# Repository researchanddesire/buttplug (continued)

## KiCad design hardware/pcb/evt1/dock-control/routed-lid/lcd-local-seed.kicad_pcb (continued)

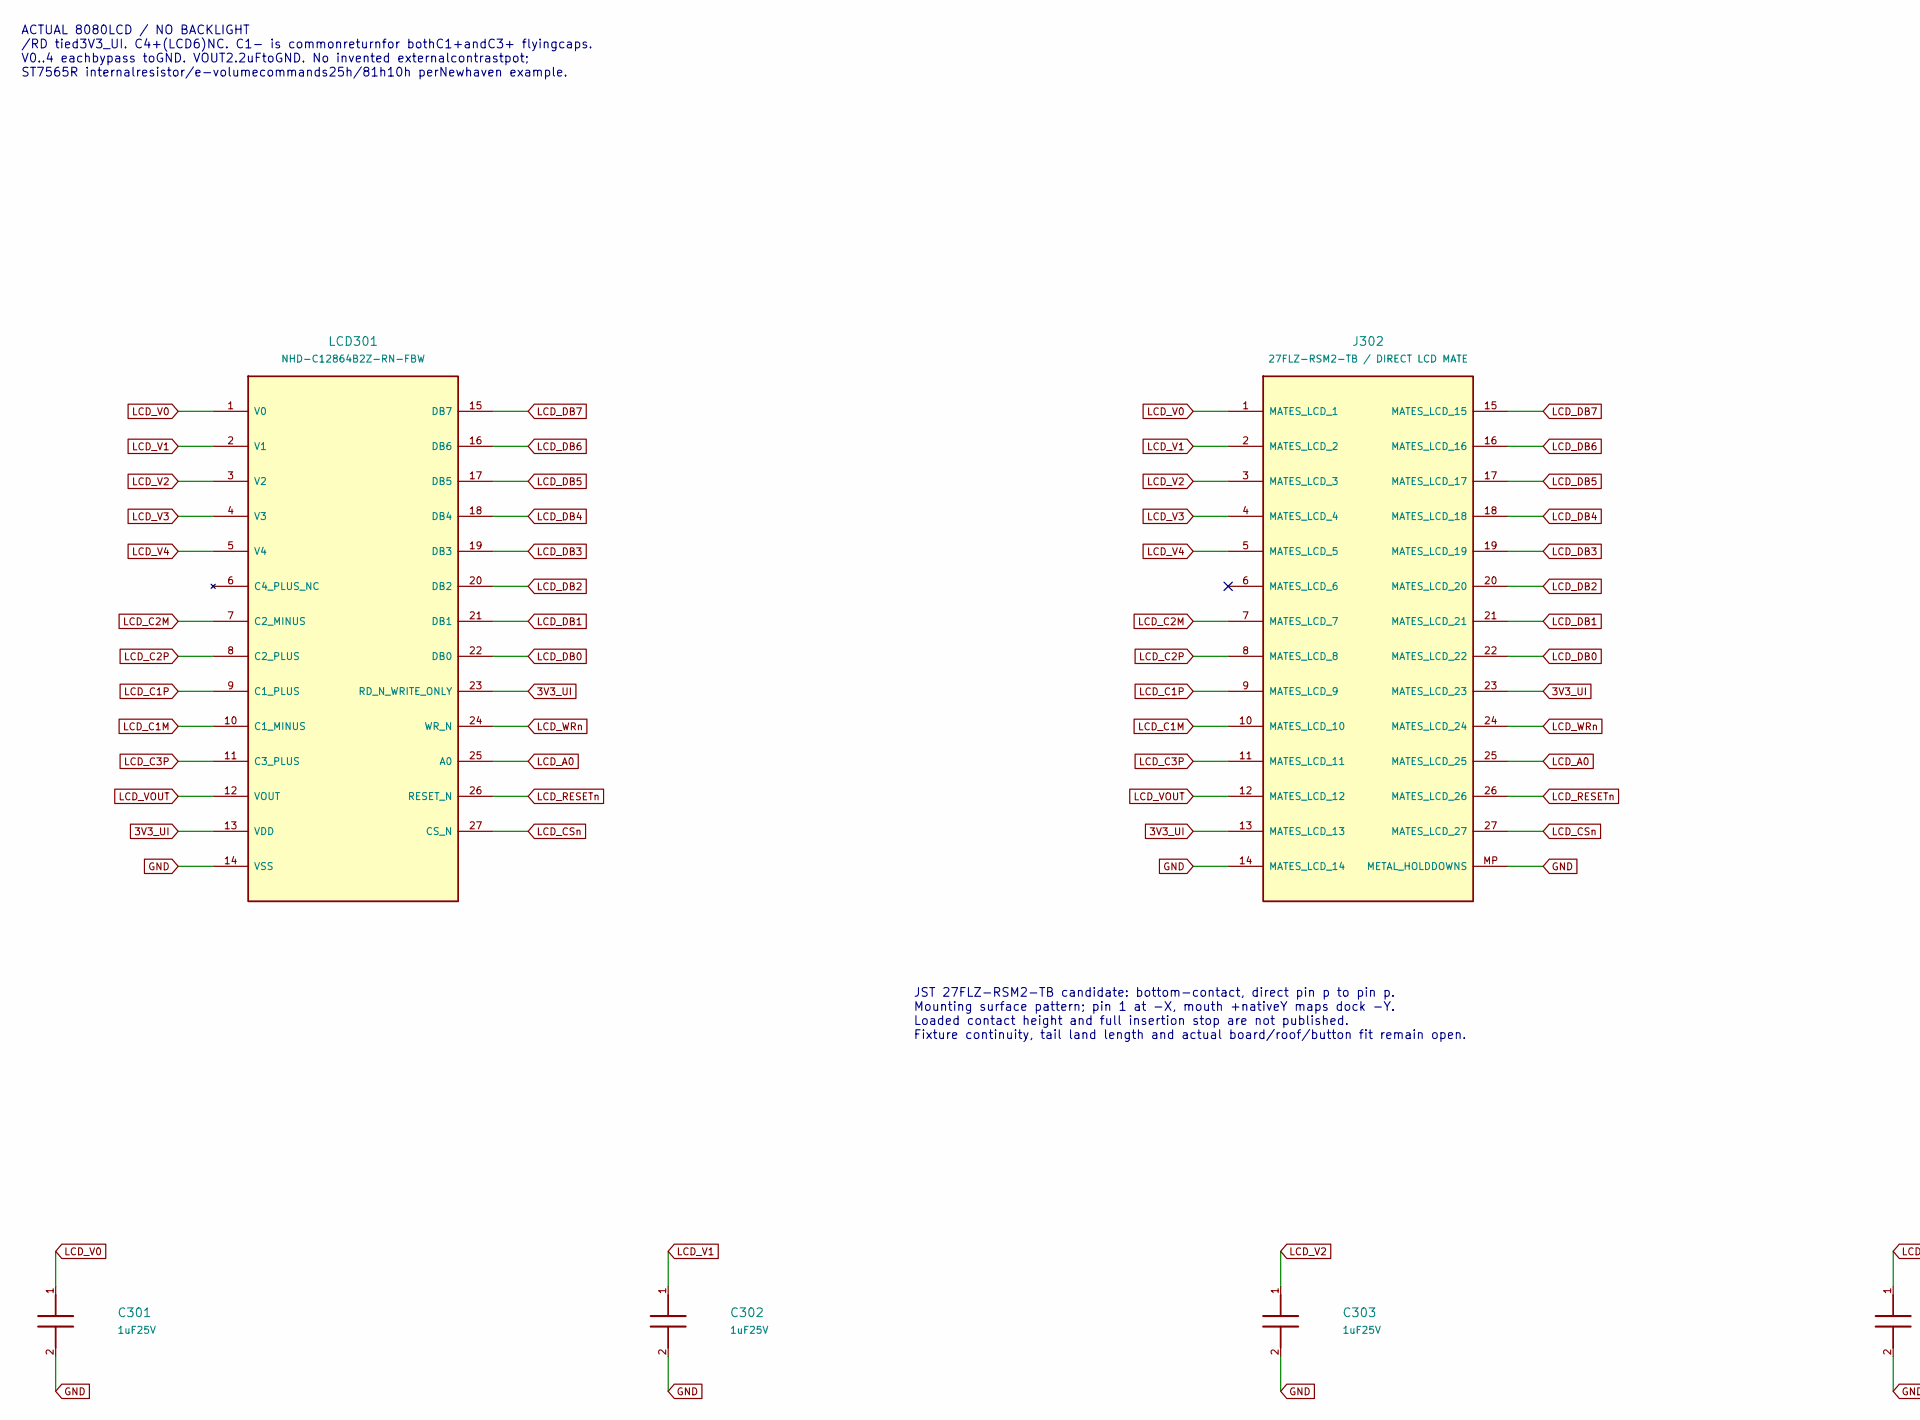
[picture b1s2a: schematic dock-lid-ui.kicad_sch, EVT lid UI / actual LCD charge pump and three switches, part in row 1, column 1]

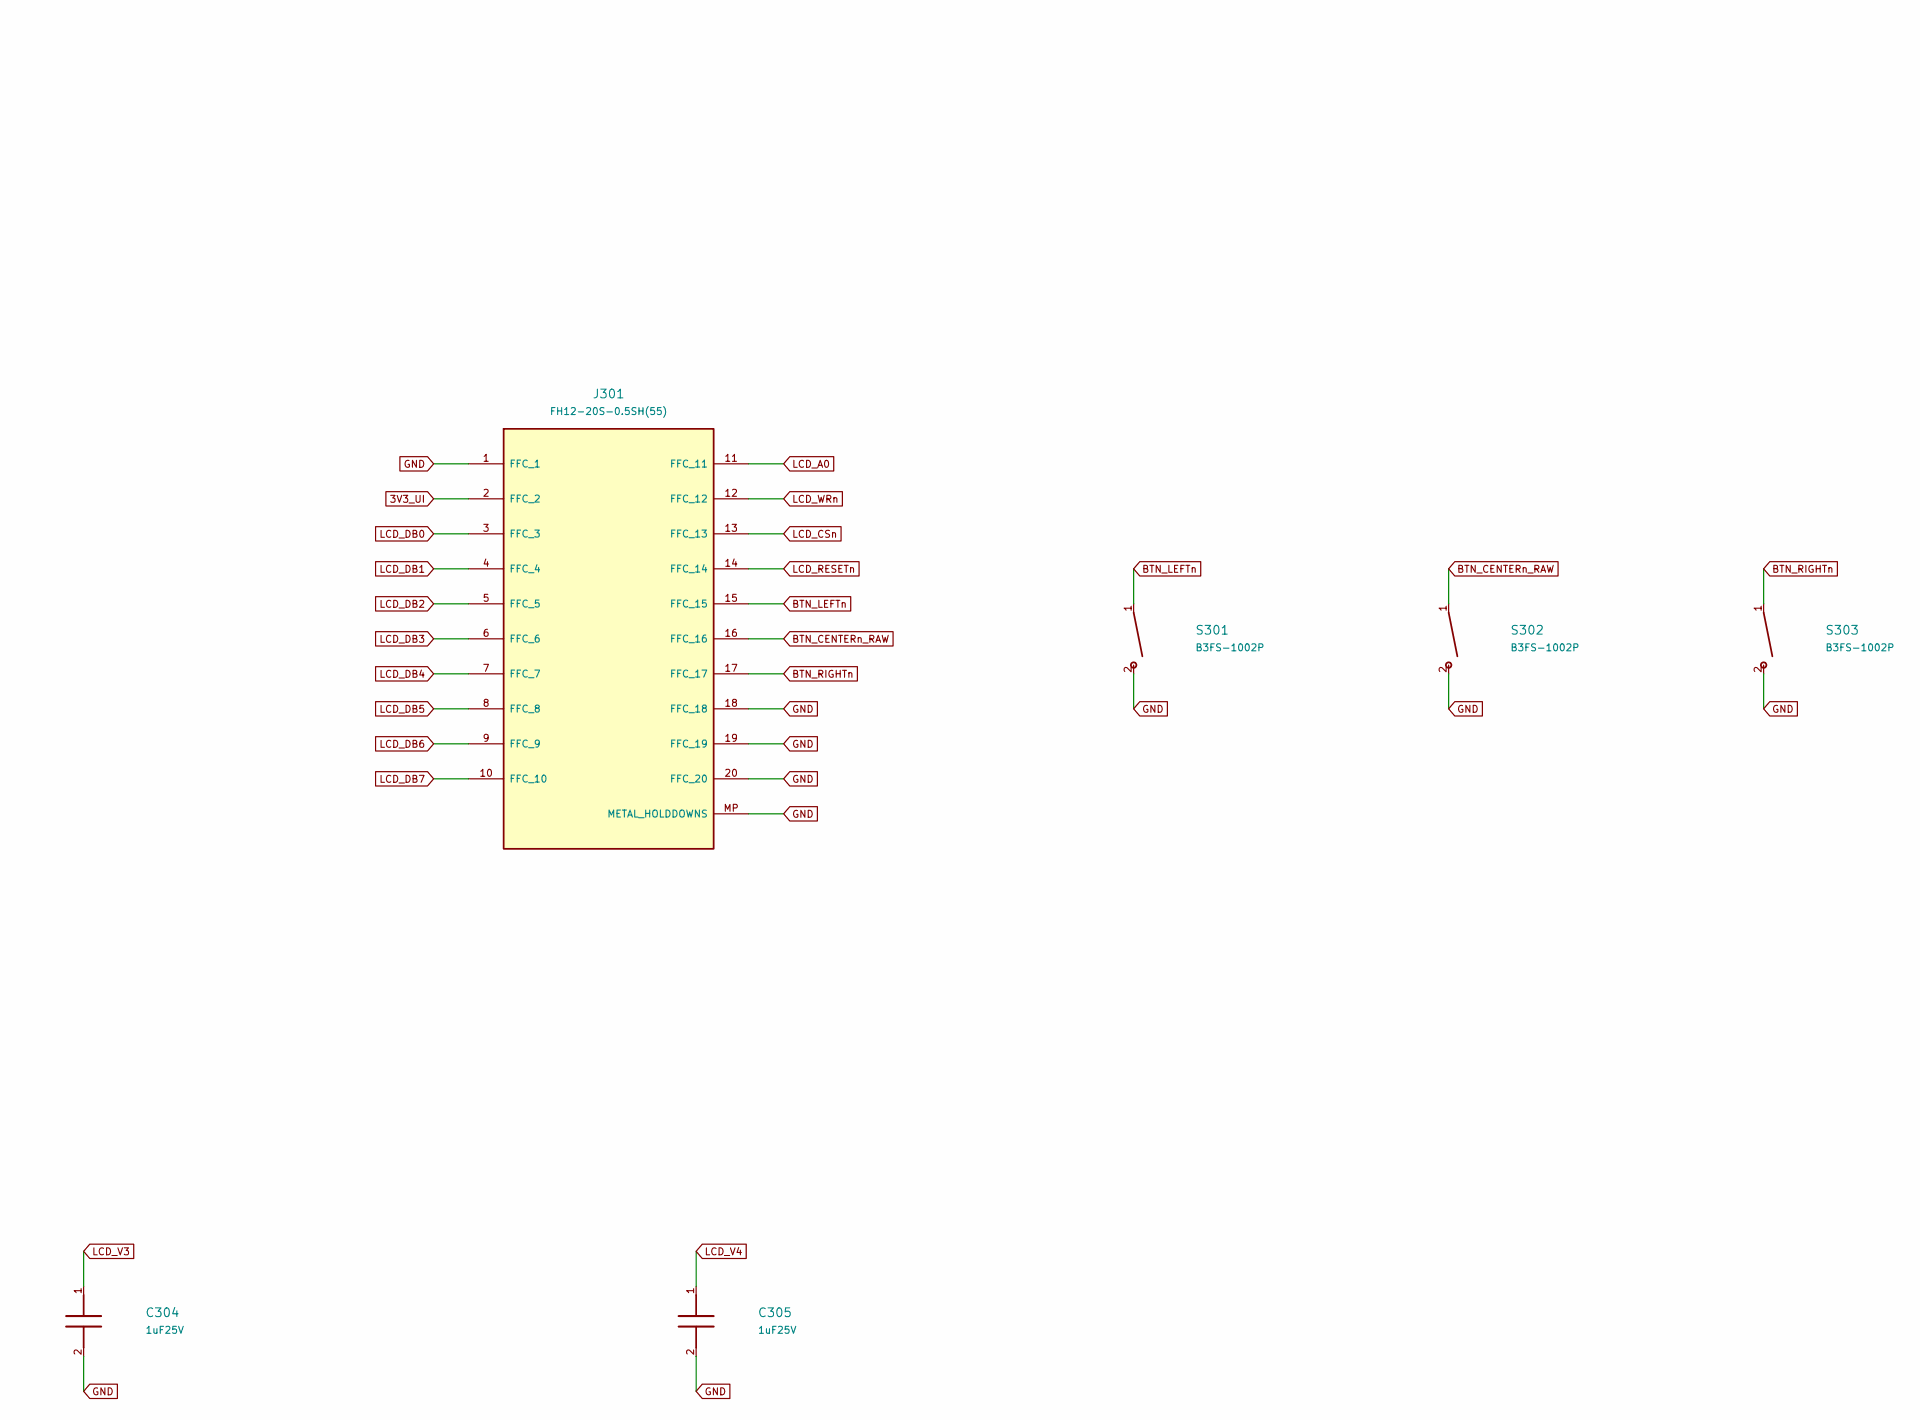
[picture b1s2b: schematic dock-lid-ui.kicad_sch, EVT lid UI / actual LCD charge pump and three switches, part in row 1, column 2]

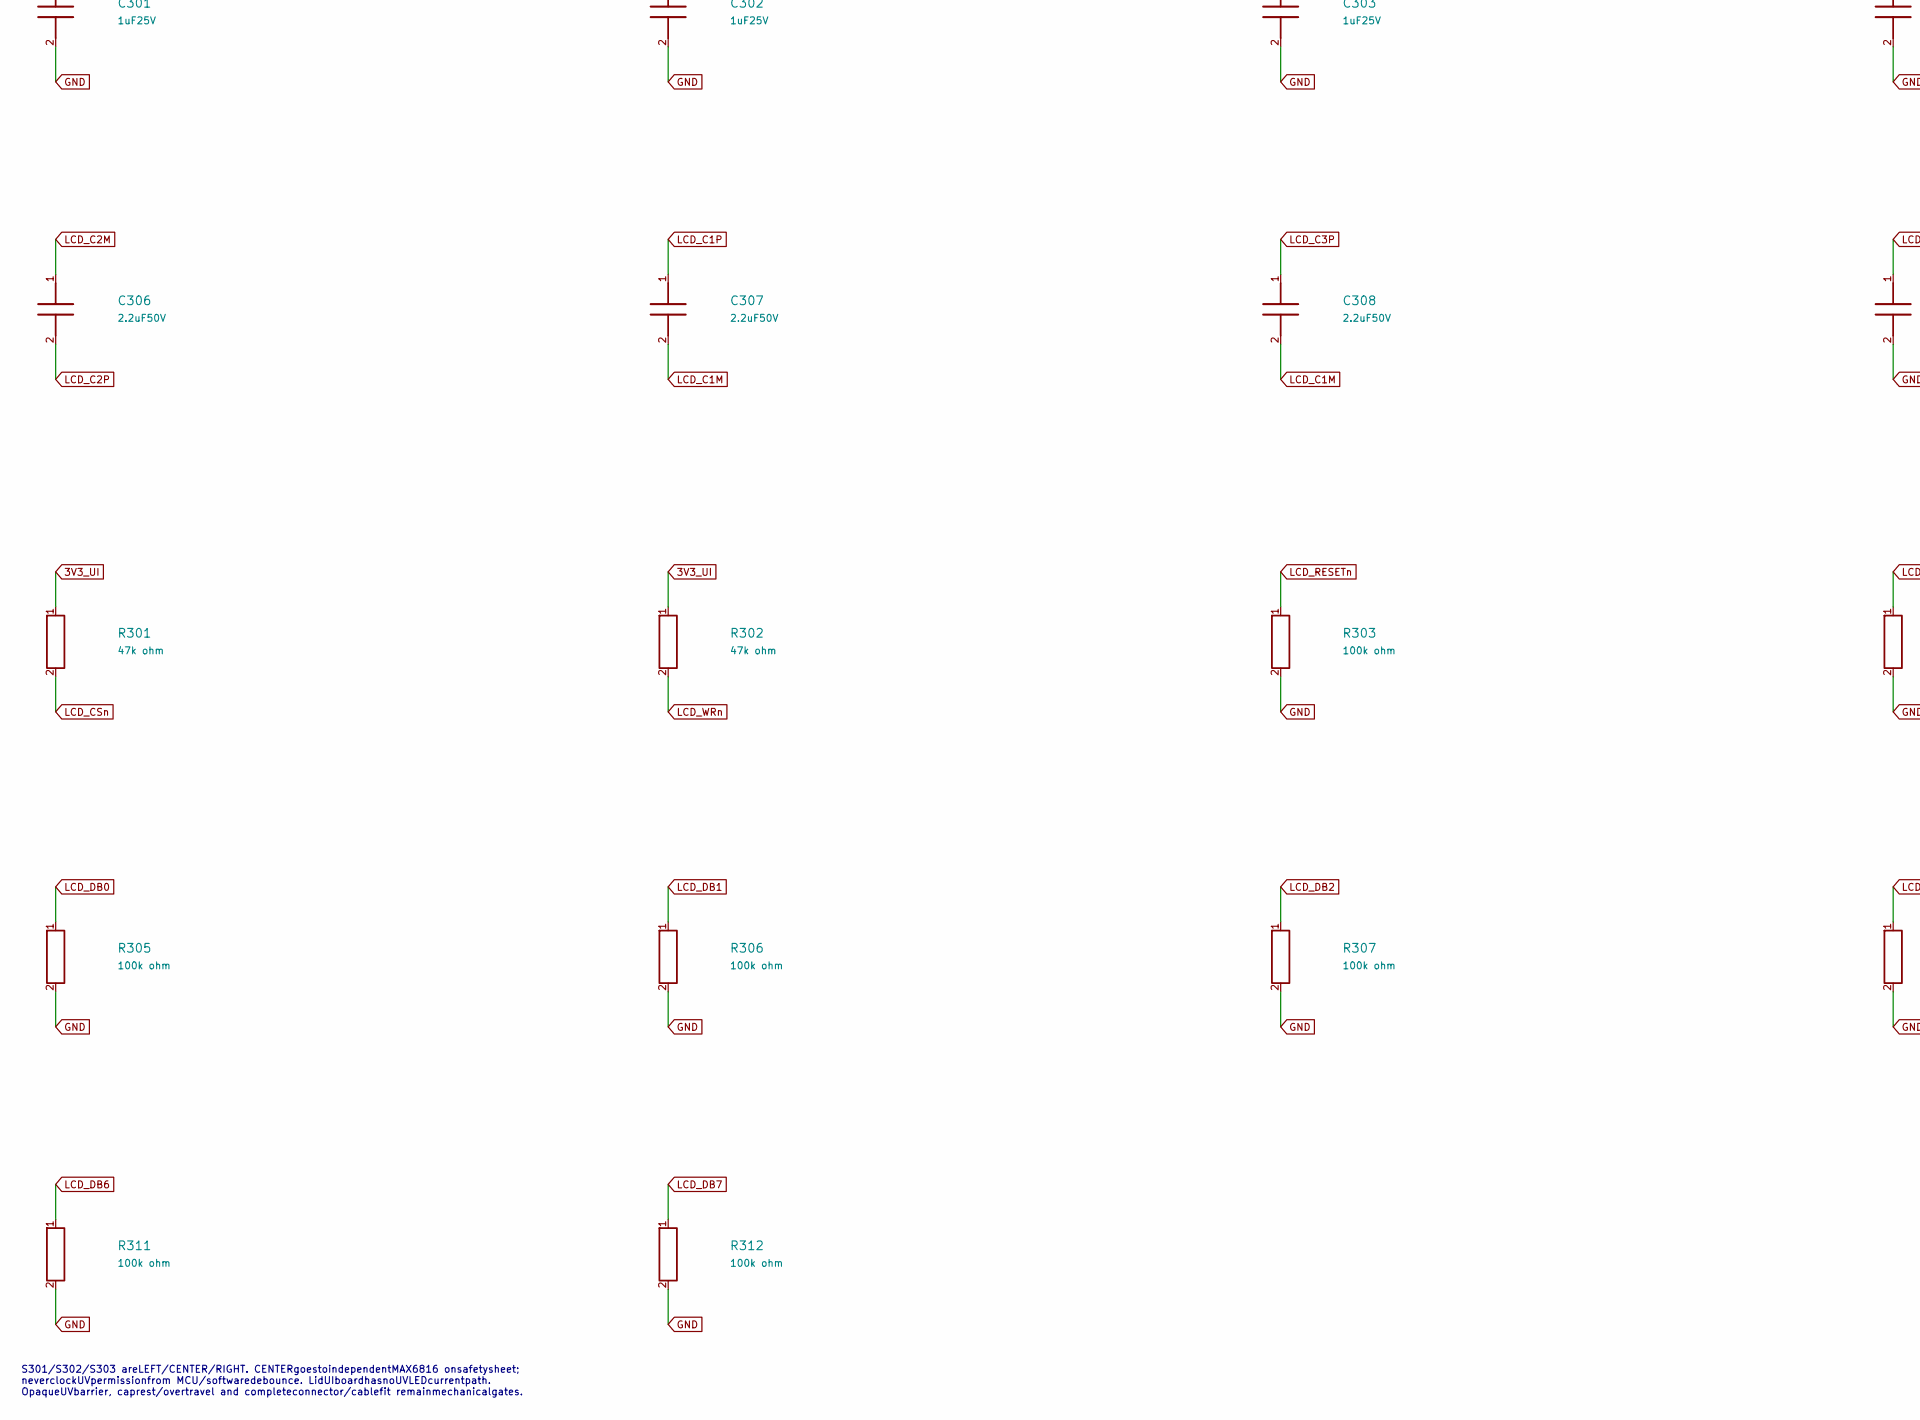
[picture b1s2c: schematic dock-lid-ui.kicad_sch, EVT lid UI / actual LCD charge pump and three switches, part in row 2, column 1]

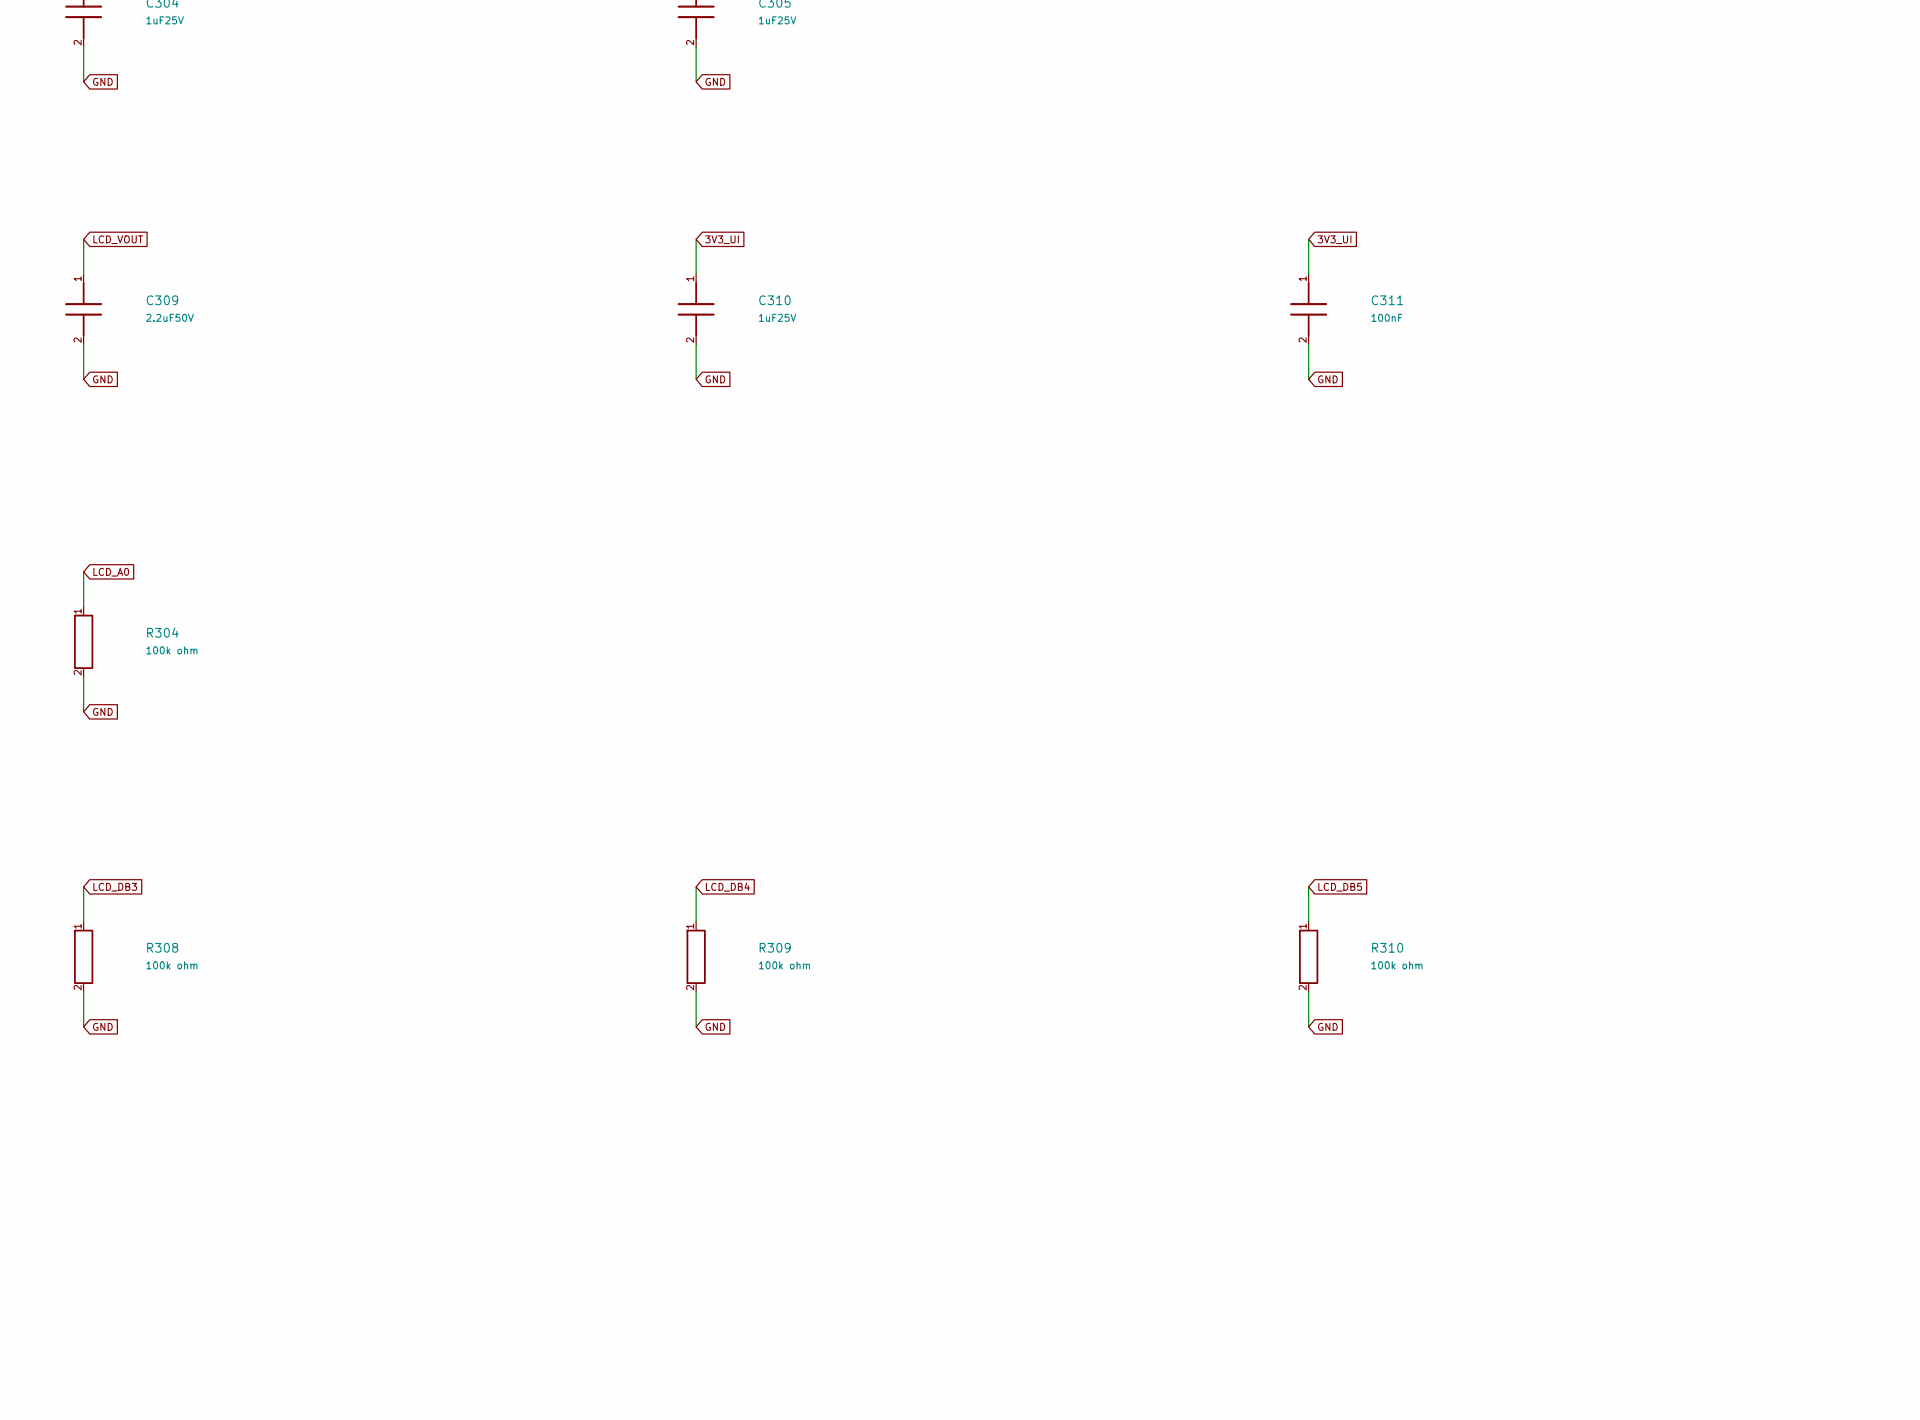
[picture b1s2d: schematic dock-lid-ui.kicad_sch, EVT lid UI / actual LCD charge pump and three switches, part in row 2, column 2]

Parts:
C301, C302, C303, C304, C305, C310: 1uF25V; C_0603_1608Metric; MPN C1608X7R1E105K080AB
C306, C307, C308, C309: 2.2uF50V; C_1206_3216Metric; MPN C3216X7R1H225K160AB
C311: 100nF; C_0402_1005Metric; MPN GRM155R71C104KA88D
J301: FH12-20S-0.5SH(55); Hirose_FH12-20S-0.5SH_1x20-1MP_P0.50mm_Horizontal; MPN FH12-20S-0.5SH(55)
J302: 27FLZ-RSM2-TB / DIRECT LCD MATE; JST_27FLZ-RSM2-TB_1x27_P0.50mm_BottomContact; MPN 27FLZ-RSM2-TB
LCD301: NHD-C12864B2Z-RN-FBW; MPN NHD-C12864B2Z-RN-FBW
R301, R302: 47k ohm; R_0603_1608Metric; MPN RC0603FR-0747KL
R303, R304, R305, R306, R307, R308, R309, R310, R311, R312: 100k ohm; R_0603_1608Metric; MPN RC0603FR-07100KL
S301, S302, S303: B3FS-1002P; SW_SPST_Omron_B3FS-100xP; MPN B3FS-1002P

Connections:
3V3_UI: C310.1, C311.1, J301.2 (FFC_2), J302.13 (MATES_LCD_13), J302.23 (MATES_LCD_23), LCD301.13 (VDD), LCD301.23 (RD_N_WRITE_ONLY), R301.1, R302.1
BTN_CENTERn_RAW: J301.16 (FFC_16), S302.1
BTN_LEFTn: J301.15 (FFC_15), S301.1
BTN_RIGHTn: J301.17 (FFC_17), S303.1
GND: C301.2, C302.2, C303.2, C304.2, C305.2, C309.2, C310.2, C311.2, J301.1 (FFC_1), J301.18 (FFC_18), J301.19 (FFC_19), J301.20 (FFC_20), J301.MP (METAL_HOLDDOWNS), J302.14 (MATES_LCD_14), J302.MP (METAL_HOLDDOWNS), LCD301.14 (VSS), R303.2, R304.2, R305.2, R306.2, R307.2, R308.2, R309.2, R310.2, R311.2, R312.2, S301.2, S302.2, S303.2
LCD_A0: J301.11 (FFC_11), J302.25 (MATES_LCD_25), LCD301.25 (A0), R304.1
LCD_C1M: C307.2, C308.2, J302.10 (MATES_LCD_10), LCD301.10 (C1_MINUS)
LCD_C1P: C307.1, J302.9 (MATES_LCD_9), LCD301.9 (C1_PLUS)
LCD_C2M: C306.1, J302.7 (MATES_LCD_7), LCD301.7 (C2_MINUS)
LCD_C2P: C306.2, J302.8 (MATES_LCD_8), LCD301.8 (C2_PLUS)
LCD_C3P: C308.1, J302.11 (MATES_LCD_11), LCD301.11 (C3_PLUS)
LCD_CSn: J301.13 (FFC_13), J302.27 (MATES_LCD_27), LCD301.27 (CS_N), R301.2
LCD_DB0: J301.3 (FFC_3), J302.22 (MATES_LCD_22), LCD301.22 (DB0), R305.1
LCD_DB1: J301.4 (FFC_4), J302.21 (MATES_LCD_21), LCD301.21 (DB1), R306.1
LCD_DB2: J301.5 (FFC_5), J302.20 (MATES_LCD_20), LCD301.20 (DB2), R307.1
LCD_DB3: J301.6 (FFC_6), J302.19 (MATES_LCD_19), LCD301.19 (DB3), R308.1
LCD_DB4: J301.7 (FFC_7), J302.18 (MATES_LCD_18), LCD301.18 (DB4), R309.1
LCD_DB5: J301.8 (FFC_8), J302.17 (MATES_LCD_17), LCD301.17 (DB5), R310.1
LCD_DB6: J301.9 (FFC_9), J302.16 (MATES_LCD_16), LCD301.16 (DB6), R311.1
LCD_DB7: J301.10 (FFC_10), J302.15 (MATES_LCD_15), LCD301.15 (DB7), R312.1
LCD_RESETn: J301.14 (FFC_14), J302.26 (MATES_LCD_26), LCD301.26 (RESET_N), R303.1
LCD_V0: C301.1, J302.1 (MATES_LCD_1), LCD301.1 (V0)
LCD_V1: C302.1, J302.2 (MATES_LCD_2), LCD301.2 (V1)
LCD_V2: C303.1, J302.3 (MATES_LCD_3), LCD301.3 (V2)
LCD_V3: C304.1, J302.4 (MATES_LCD_4), LCD301.4 (V3)
LCD_V4: C305.1, J302.5 (MATES_LCD_5), LCD301.5 (V4)
LCD_VOUT: C309.1, J302.12 (MATES_LCD_12), LCD301.12 (VOUT)
LCD_WRn: J301.12 (FFC_12), J302.24 (MATES_LCD_24), LCD301.24 (WR_N), R302.2

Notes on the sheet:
ACTUAL 8080LCD / NO BACKLIGHT /RD tied3V3_UI. C4+(LCD6)NC. C1- is commonreturnfor bothC1+andC3+ flyingcaps. V0..4 eachbypass toGND. VOUT2.2uFtoGND. No invented externalcontrastpot; ST7565R internalresistor/e-volumecommands25h/81h10h perNewhaven example.
JST 27FLZ-RSM2-TB candidate: bottom-contact, direct pin p to pin p. Mounting surface pattern; pin 1 at -X, mouth +nativeY maps dock -Y. Loaded contact height and full insertion stop are not published. Fixture continuity, tail land length and actual board/roof/button fit remain open.
S301/S302/S303 areLEFT/CENTER/RIGHT. CENTERgoestoindependentMAX6816 onsafetysheet; neverclockUVpermissionfrom MCU/softwaredebounce. LidUIboardhasnoUVLEDcurrentpath. OpaqueUVbarrier, caprest/overtravel and completeconnector/cablefit remainmechanicalgates.

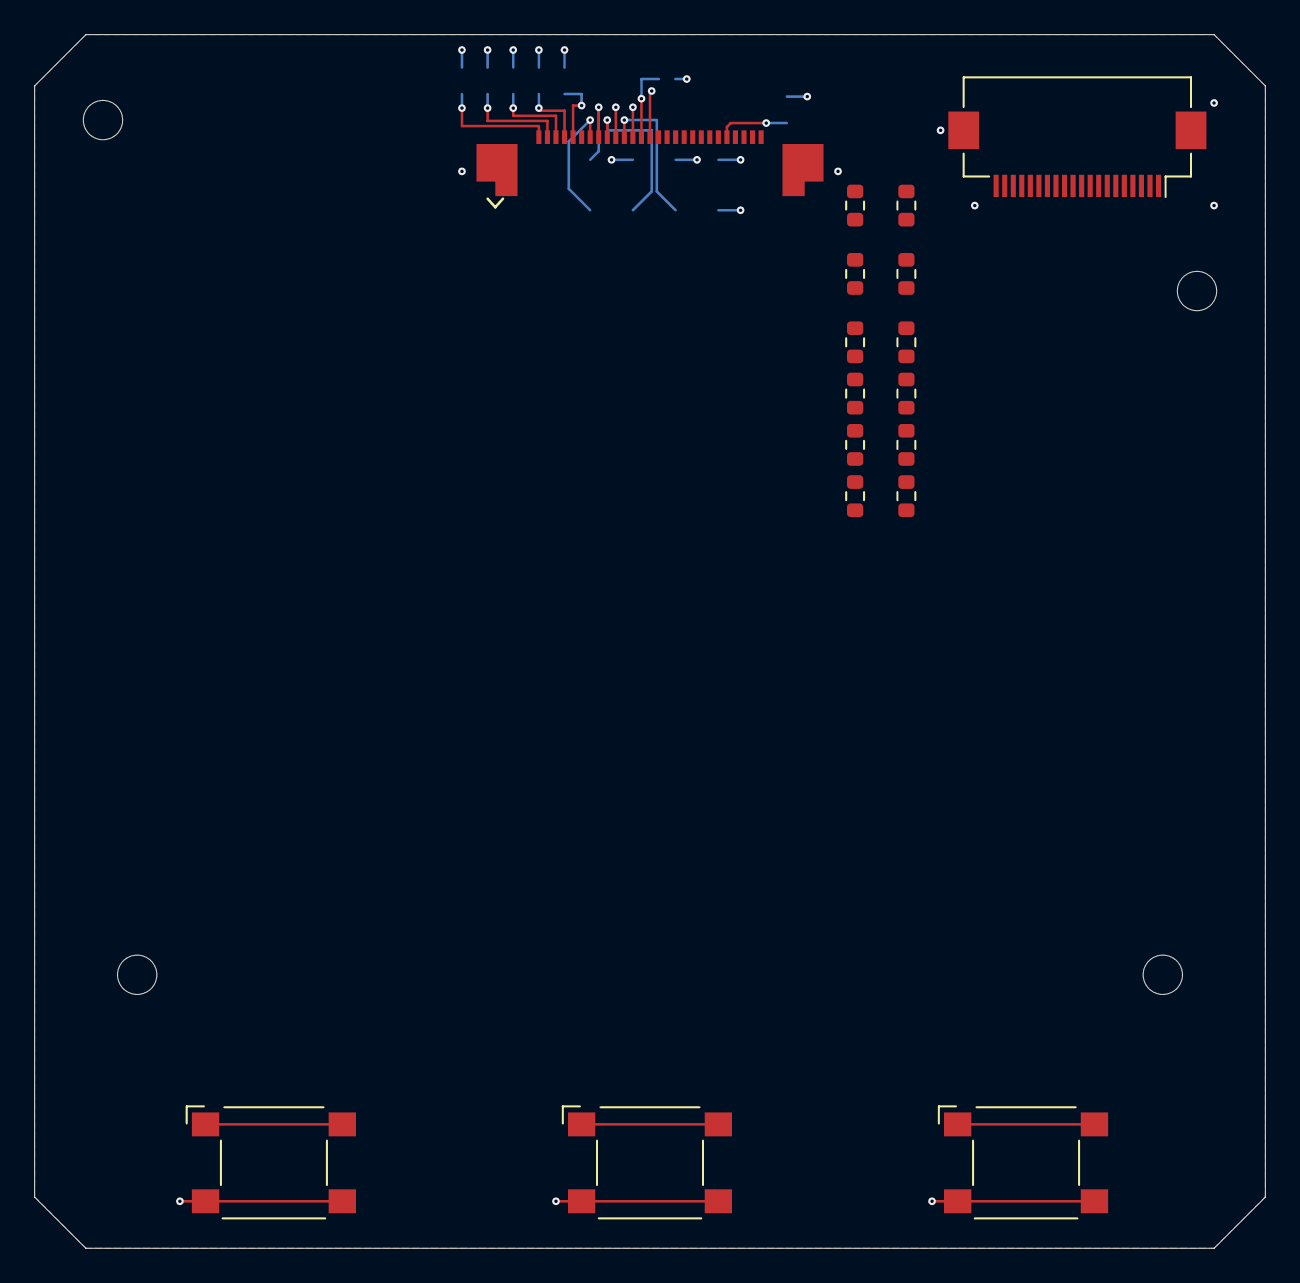
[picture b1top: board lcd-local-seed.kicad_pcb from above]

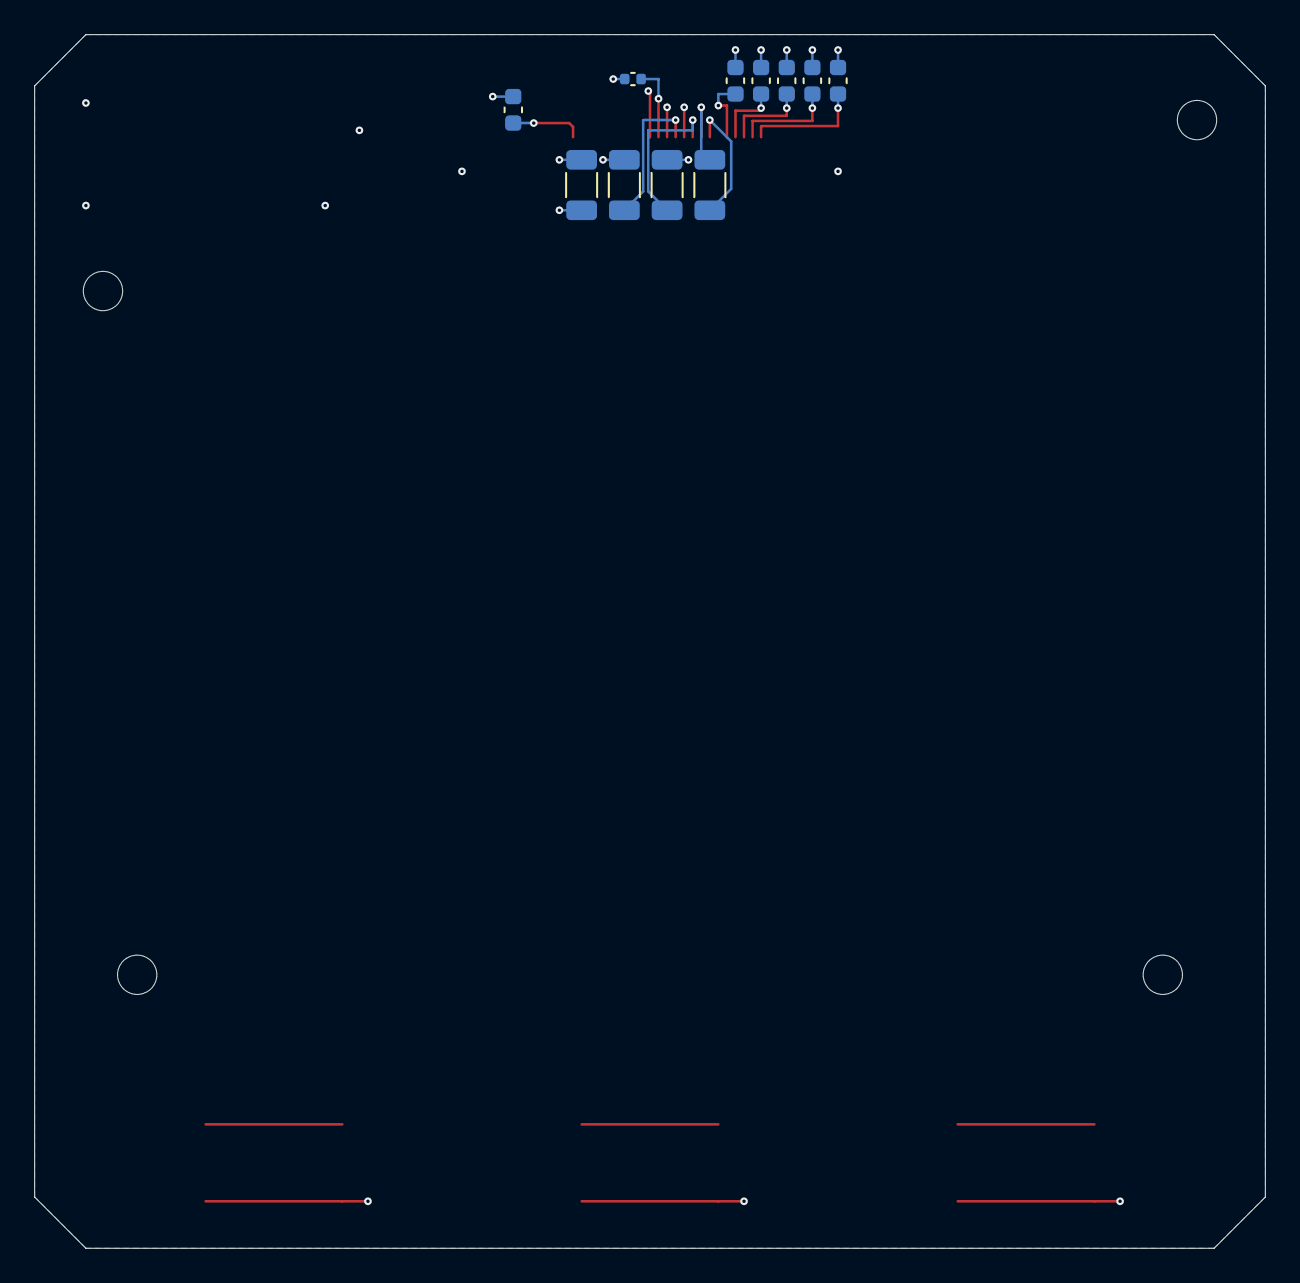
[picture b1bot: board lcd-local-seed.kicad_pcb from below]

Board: 4 copper layers, 72.0 x 71.0 mm, 32 parts (11 on the bottom side), 28 nets.

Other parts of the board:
H301, H302, H303, H304: M2 NPTH2.3/R3 hardware; MountingHole_2.3mm_M2_R3_Hardware
